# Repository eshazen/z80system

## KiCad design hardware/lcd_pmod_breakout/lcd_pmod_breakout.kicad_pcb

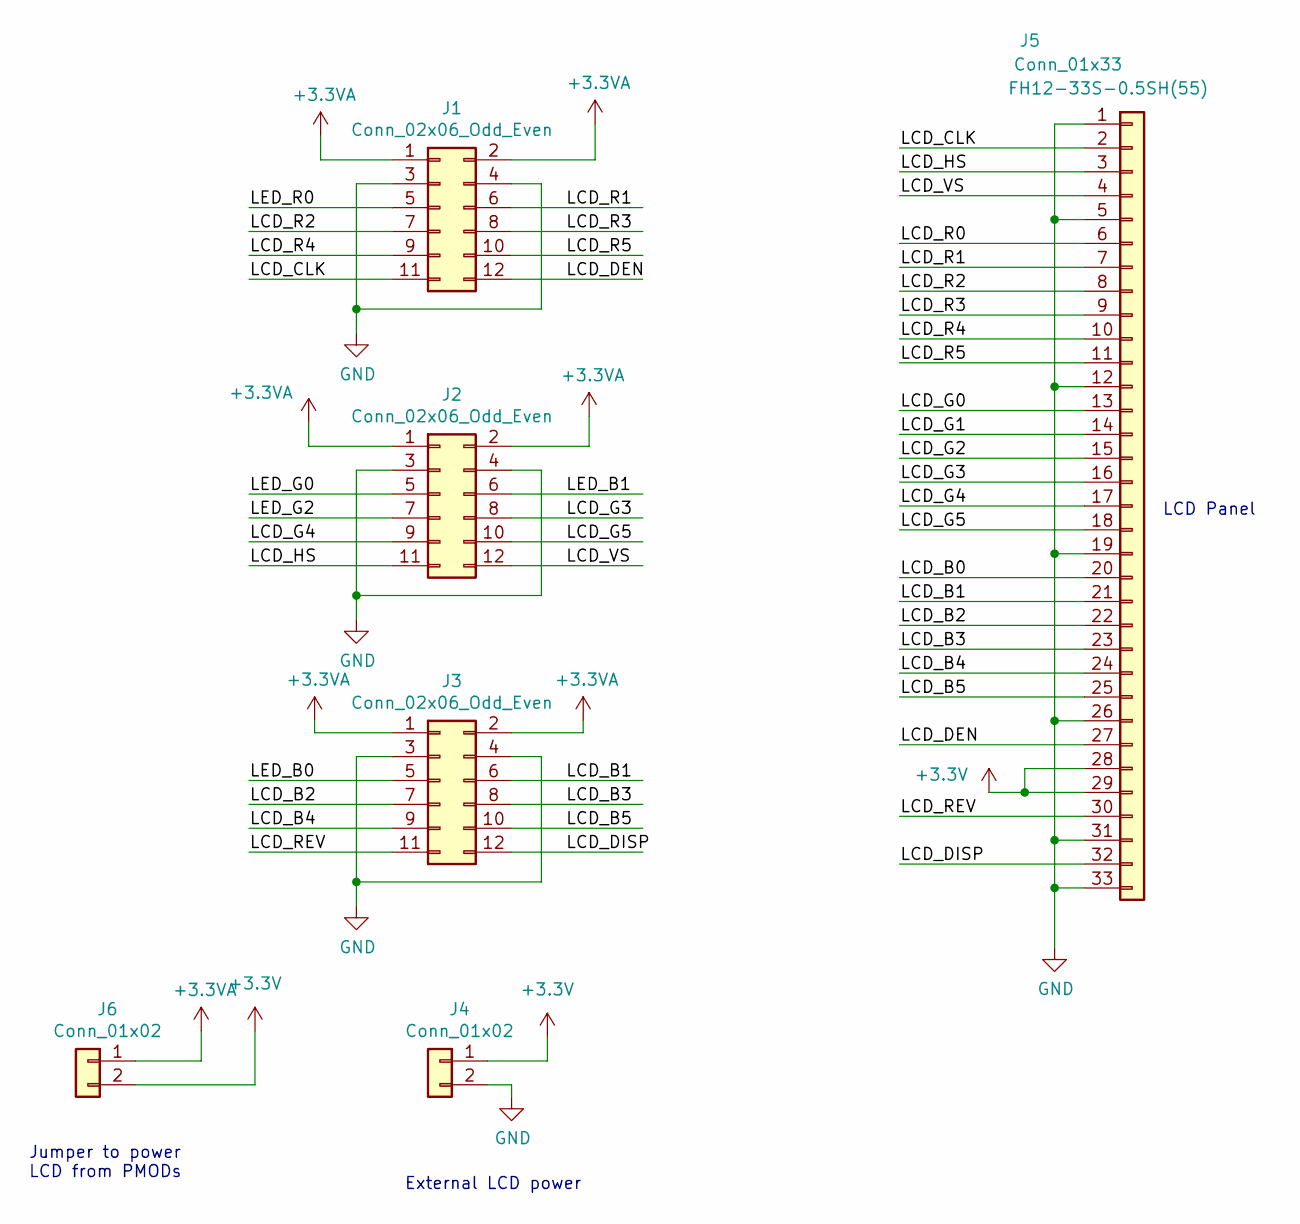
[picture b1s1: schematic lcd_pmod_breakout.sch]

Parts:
J1, J2, J3: Conn_02x06_Odd_Even; PinHeader_2x06_P2.54mm_Vertical
J4, J6: Conn_01x02; PinHeader_1x02_P2.54mm_Vertical
J5: Conn_01x33; FH12-33S-0.5

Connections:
+3.3VA: J1.1, J1.2, J2.1, J2.2, J3.1, J3.2, J6.1
+3V3: J4.1, J5.28, J5.29, J6.2
/LCD_B0: J5.20
/LCD_B1: J3.6, J5.21
/LCD_B2: J3.7, J5.22
/LCD_B3: J3.8, J5.23
/LCD_B4: J3.9, J5.24
/LCD_B5: J3.10, J5.25
/LCD_CLK: J1.11, J5.2
/LCD_DEN: J1.12, J5.27
/LCD_DISP: J3.12, J5.32
/LCD_G0: J5.13
/LCD_G1: J5.14
/LCD_G2: J5.15
/LCD_G3: J2.8, J5.16
/LCD_G4: J2.9, J5.17
/LCD_G5: J2.10, J5.18
/LCD_HS: J2.11, J5.3
/LCD_R0: J5.6
/LCD_R1: J1.6, J5.7
/LCD_R2: J1.7, J5.8
/LCD_R3: J1.8, J5.9
/LCD_R4: J1.9, J5.10
/LCD_R5: J1.10, J5.11
/LCD_REV: J3.11, J5.30
/LCD_VS: J2.12, J5.4
/LED_B0: J3.5
/LED_B1: J2.6
/LED_G0: J2.5
/LED_G2: J2.7
/LED_R0: J1.5
GND: J1.3, J1.4, J2.3, J2.4, J3.3, J3.4, J4.2, J5.1, J5.5, J5.12, J5.19, J5.26, J5.31, J5.33

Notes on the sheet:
LCD Panel
Jumper to power LCD from PMODs
External LCD power

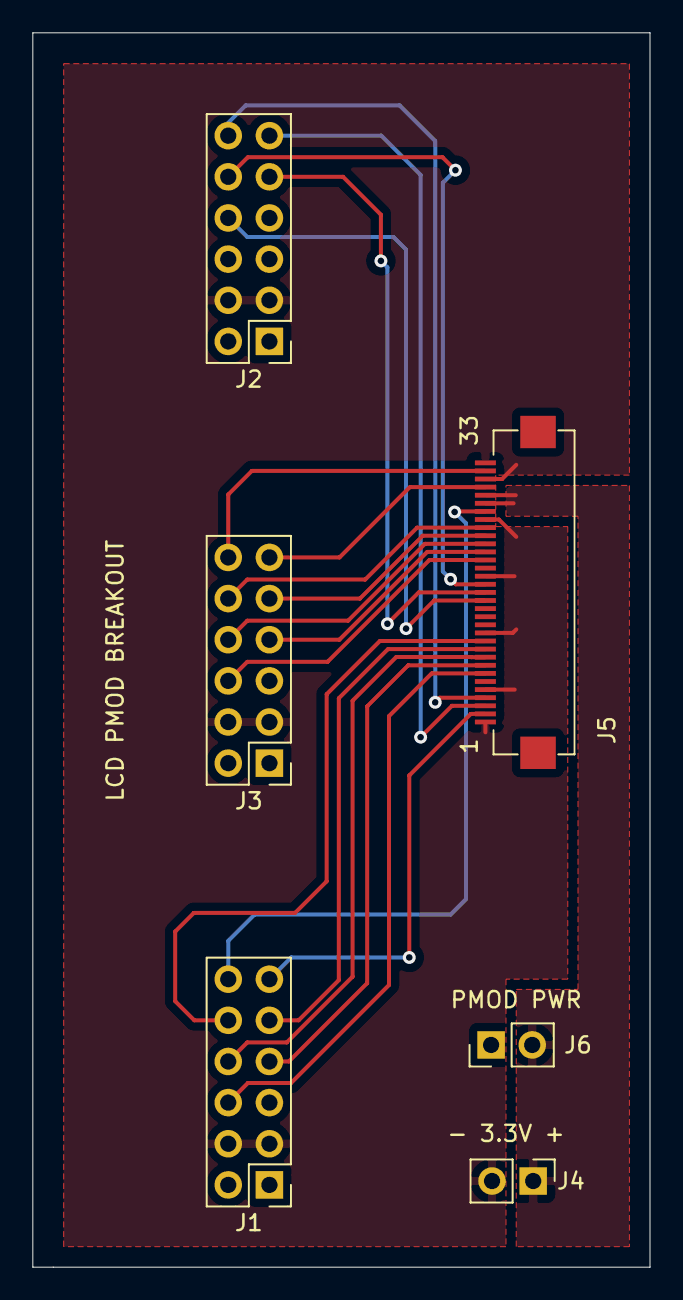
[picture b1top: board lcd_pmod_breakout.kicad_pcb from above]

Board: 2 copper layers, 38.1 x 76.2 mm, 6 parts (0 on the bottom side), 22 nets.

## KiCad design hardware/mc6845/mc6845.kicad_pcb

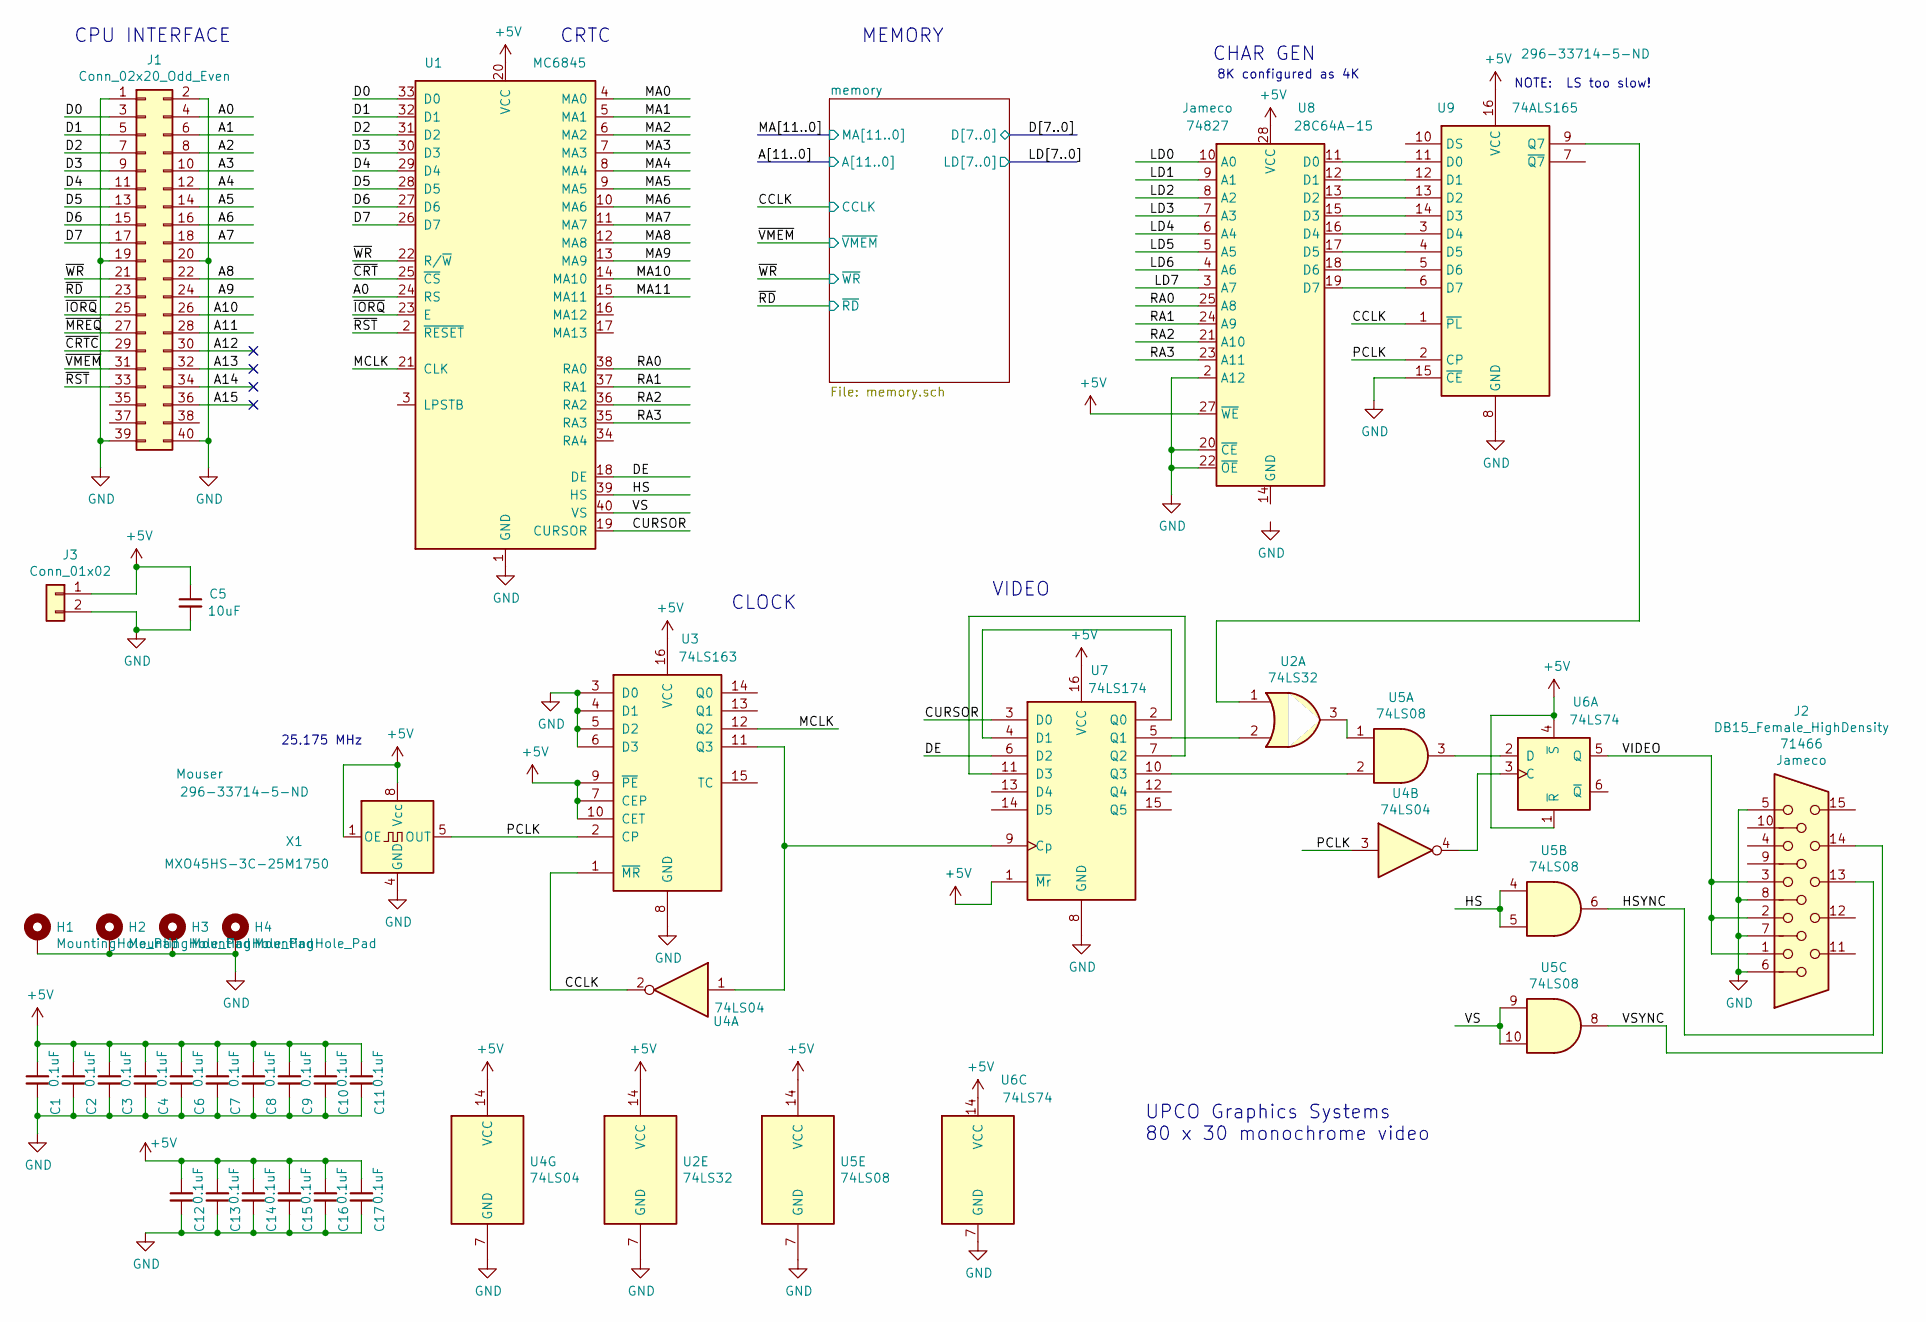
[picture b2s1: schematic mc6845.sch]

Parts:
C1, C2, C3, C4, C6, C7, C8, C9, C10, C11, C12, C13, C14, C15, C16, C17: 0.1uF; C_Disc_D3.0mm_W1.6mm_P2.50mm
C5: 10uF; CP_Radial_Tantal_D5.5mm_P5.00mm
H1, H2, H3, H4: MountingHole_Pad; MountingHole_2.7mm_M2.5_DIN965_Pad
J1: Conn_02x20_Odd_Even; PinSocket_2x20_P2.54mm_Vertical
J2: DB15_Female_HighDensity; DSUB-15-HD_Female_Horizontal_P2.29x2.54mm_EdgePinOffset9.40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
J3: Conn_01x02; Molex_Mini-Fit_Jr_5566-02A_2x01_P4.20mm_Vertical
U1: MC6845; DIP-40_W15.24mm
U2: 74LS32; DIP-14_W7.62mm_Socket_LongPads
U3: 74LS163; DIP-16_W7.62mm_Socket_LongPads
U4: 74LS04; DIP-14_W7.62mm_Socket_LongPads
U5: 74LS08; DIP-14_W7.62mm_Socket_LongPads
U6: 74LS74; DIP-14_W7.62mm_Socket_LongPads
U7: 74LS174; DIP-16_W7.62mm_Socket_LongPads
U8: 28C64A-15; DIP-28_W15.24mm
U9: 74ALS165; DIP-16_W7.62mm_Socket_LongPads
X1: MXO45HS-3C-25M1750; DIP-8_W7.62mm_LongPads

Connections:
+5V: C1.1, C2.1, C3.1, C4.1, C5.1, C6.1, C7.1, C8.1, C9.1, C10.1, C11.1, C12.1, C13.1, C14.1, C15.1, C16.1, C17.1, J3.1, U1.20 (VCC), U2.14 (VCC), U3.7 (CEP), U3.9 (~PE), U3.10 (CET), U3.16 (VCC), U4.14 (VCC), U5.14 (VCC), U6.1 (~R), U6.4 (~S), U6.14 (VCC), U7.1 (~Mr), U7.16 (VCC), U8.27 (~WE), U8.28 (VCC), U9.16 (VCC), X1.1 (OE), X1.8 (Vcc); also elsewhere on the board
/A0: J1.4, U1.24 (RS); also elsewhere on the board
/A1: J1.6; also elsewhere on the board
/A2: J1.8; also elsewhere on the board
/A3: J1.10; also elsewhere on the board
/A4: J1.12; also elsewhere on the board
/A5: J1.14; also elsewhere on the board
/A6: J1.16; also elsewhere on the board
/A7: J1.18; also elsewhere on the board
/A8: J1.22; also elsewhere on the board
/A9: J1.24; also elsewhere on the board
/A10: J1.26; also elsewhere on the board
/A11: J1.28; also elsewhere on the board
/A12: J1.30
/A13: J1.32
/A14: J1.34
/A15: J1.36
/CCLK: U3.1 (~MR), U4.2, U9.1 (~PL); also elsewhere on the board
/CURSOR: U1.19 (CURSOR), U7.3 (D0)
/D0: J1.3, U1.33 (D0); also elsewhere on the board
/D1: J1.5, U1.32 (D1); also elsewhere on the board
/D2: J1.7, U1.31 (D2); also elsewhere on the board
/D3: J1.9, U1.30 (D3); also elsewhere on the board
/D4: J1.11, U1.29 (D4); also elsewhere on the board
/D5: J1.13, U1.28 (D5); also elsewhere on the board
/D6: J1.15, U1.27 (D6); also elsewhere on the board
/D7: J1.17, U1.26 (D7); also elsewhere on the board
/DE: U1.18 (DE), U7.6 (D2)
/HS: U1.39 (HS), U5.4, U5.5
/HSYNC: J2.13, U5.6
/LD0: U8.10 (A0); also elsewhere on the board
/LD1: U8.9 (A1); also elsewhere on the board
/LD2: U8.8 (A2); also elsewhere on the board
/LD3: U8.7 (A3); also elsewhere on the board
/LD4: U8.6 (A4); also elsewhere on the board
/LD5: U8.5 (A5); also elsewhere on the board
/LD6: U8.4 (A6); also elsewhere on the board
/LD7: U8.3 (A7); also elsewhere on the board
/MA0: U1.4 (MA0); also elsewhere on the board
/MA1: U1.5 (MA1); also elsewhere on the board
/MA2: U1.6 (MA2); also elsewhere on the board
/MA3: U1.7 (MA3); also elsewhere on the board
/MA4: U1.8 (MA4); also elsewhere on the board
/MA5: U1.9 (MA5); also elsewhere on the board
/MA6: U1.10 (MA6); also elsewhere on the board
/MA7: U1.11 (MA7); also elsewhere on the board
/MA8: U1.12 (MA8); also elsewhere on the board
/MA9: U1.13 (MA9); also elsewhere on the board
/MA10: U1.14 (MA10); also elsewhere on the board
/MA11: U1.15 (MA11); also elsewhere on the board
/MCLK: U1.21 (CLK), U3.12 (Q2)
/PCLK: U3.2 (CP), U4.3, U9.2 (CP), X1.5 (OUT)
/RA0: U1.38 (RA0), U8.25 (A8)
/RA1: U1.37 (RA1), U8.24 (A9)
/RA2: U1.36 (RA2), U8.21 (A10)
/RA3: U1.35 (RA3), U8.23 (A11)
/VIDEO: J2.1, J2.2, J2.3, U6.5 (Q)
/VS: U1.40 (VS), U5.9, U5.10
/VSYNC: J2.14, U5.8
/~CRT: U1.25 (~CS)
/~CRTC: J1.29
/~IORQ: J1.25, U1.23 (E)
/~MREQ: J1.27
/~RD: J1.23; also elsewhere on the board
/~RST: J1.33, U1.2 (~RESET)
/~VMEM: J1.31; also elsewhere on the board
/~WR: J1.21, U1.22 (R/~W); also elsewhere on the board
GND: C1.2, C2.2, C3.2, C4.2, C5.2, C6.2, C7.2, C8.2, C9.2, C10.2, C11.2, C12.2, C13.2, C14.2, C15.2, C16.2, C17.2, H1.1, H2.1, H3.1, H4.1, J1.1, J1.2, J1.19, J1.20, J1.39, J1.40, J2.5, J2.6, J2.7, J2.8, J3.2, U1.1 (GND), U2.7 (GND), U3.3 (D0), U3.4 (D1), U3.5 (D2), U3.6 (D3), U3.8 (GND), U4.7 (GND), U5.7 (GND), U6.7 (GND), U7.8 (GND), U8.2 (A12), U8.20 (~CE), U8.22 (~OE), U9.8 (GND), U9.15 (~CE), X1.4 (GND); also elsewhere on the board
unnamed: U2.1, U9.9 (Q7)
unnamed: U2.2, U7.5 (Q1)
unnamed: U2.3, U5.1
unnamed: U3.11 (Q3), U4.1, U7.9 (Cp)
unnamed: U4.4, U6.3 (C)
unnamed: U5.2, U7.10 (Q3)
unnamed: U5.3, U6.2 (D)
unnamed: U7.2 (Q0), U7.4 (D1)
unnamed: U7.7 (Q2), U7.11 (D3)
unnamed: U8.11 (D0), U9.11 (D0)
unnamed: U8.12 (D1), U9.12 (D1)
unnamed: U8.13 (D2), U9.13 (D2)
unnamed: U8.15 (D3), U9.14 (D3)
unnamed: U8.16 (D4), U9.3 (D4)
unnamed: U8.17 (D5), U9.4 (D5)
unnamed: U8.18 (D6), U9.5 (D6)
unnamed: U8.19 (D7), U9.6 (D7)

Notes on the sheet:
CPU INTERFACE
NOTE: LS too slow!
CLOCK
VIDEO
CRTC
MEMORY
CHAR GEN
25.175 MHz
8K configured as 4K
UPCO Graphics Systems 80 x 30 monochrome video

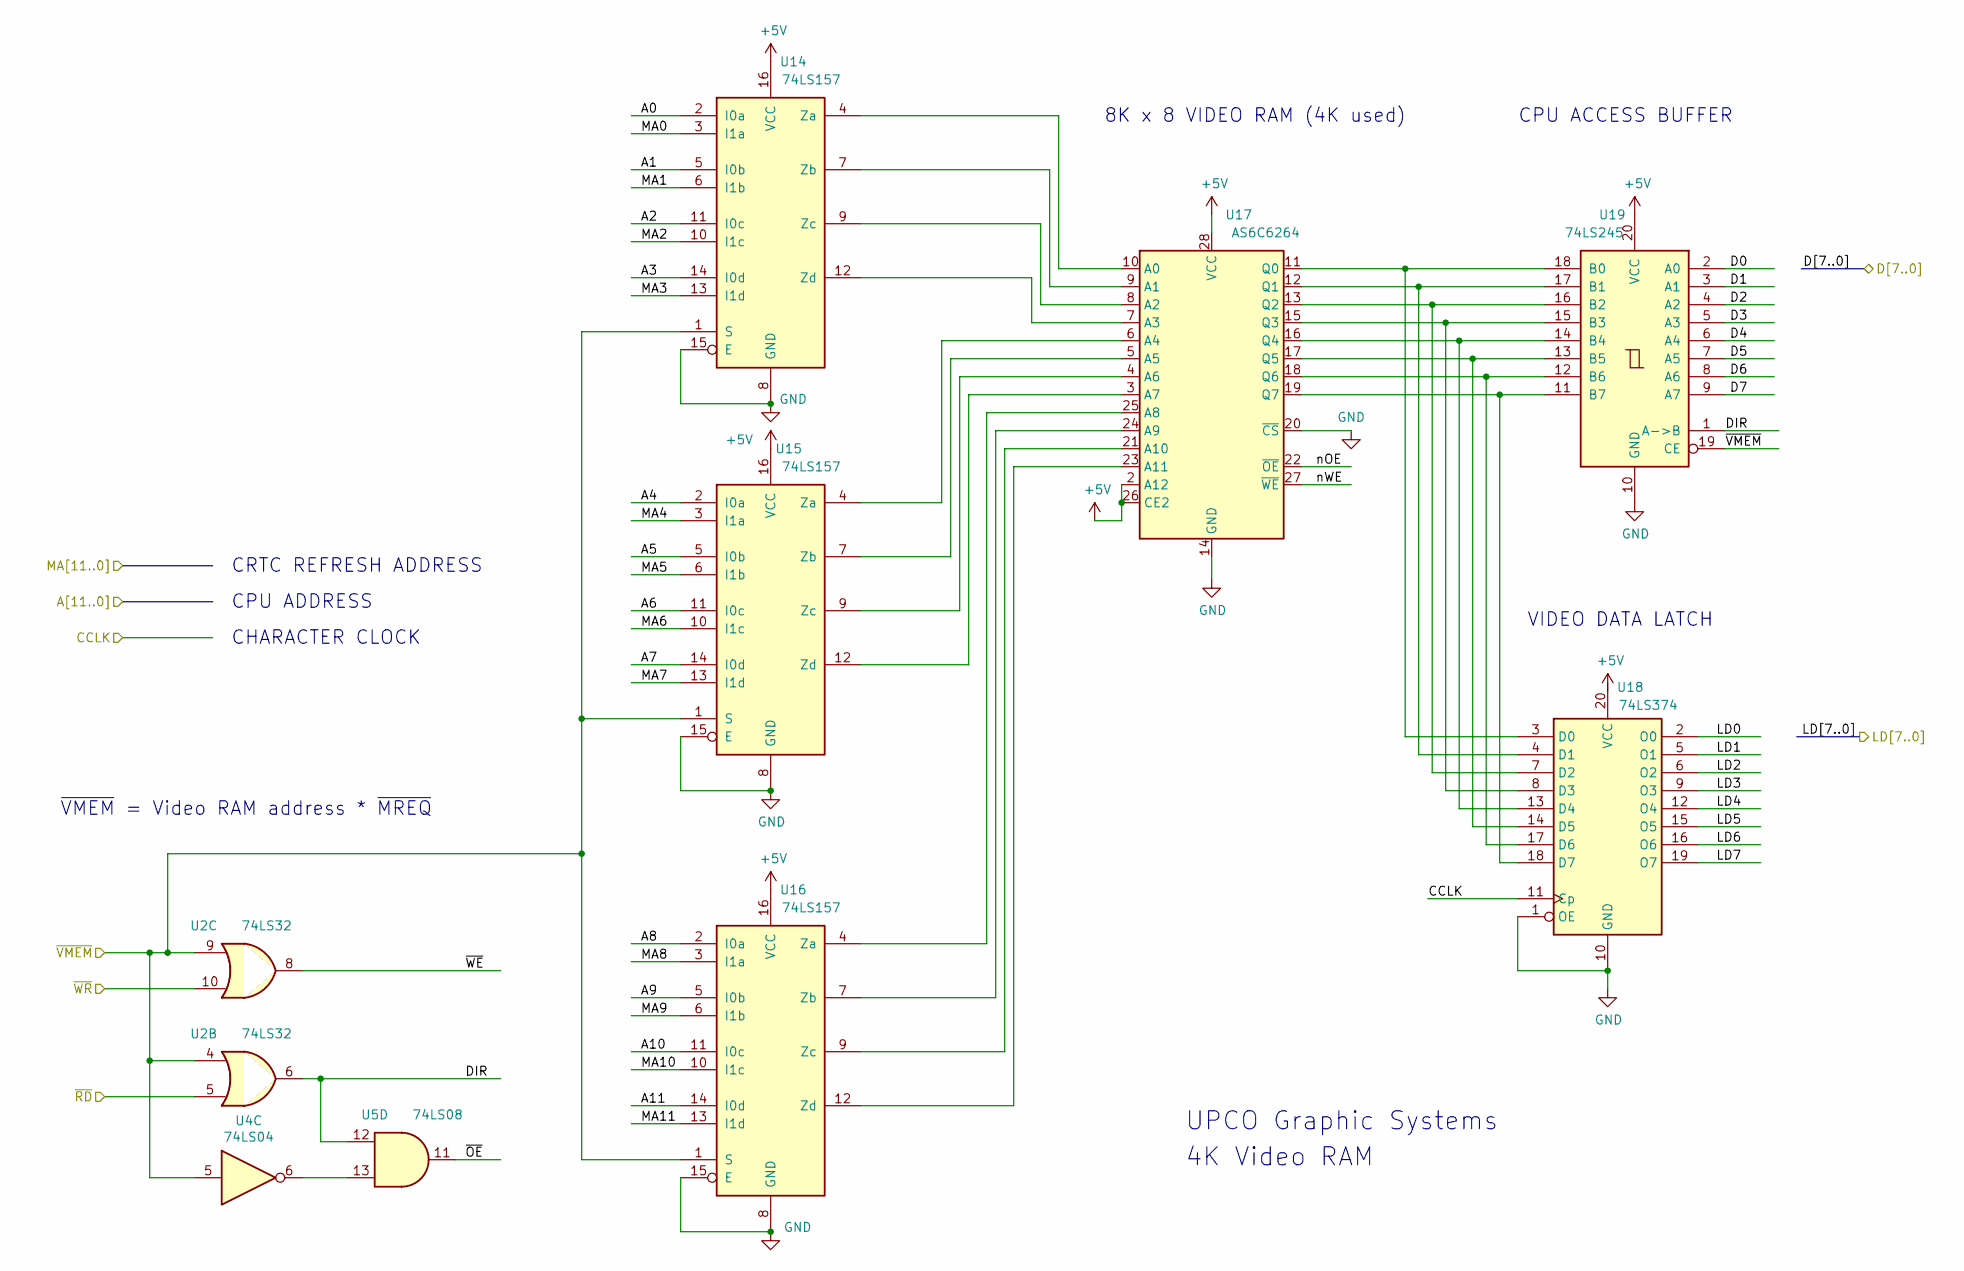
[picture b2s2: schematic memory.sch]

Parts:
U2: 74LS32; DIP-14_W7.62mm_Socket_LongPads
U4: 74LS04; DIP-14_W7.62mm_Socket_LongPads
U5: 74LS08; DIP-14_W7.62mm_Socket_LongPads
U14, U15, U16: 74LS157; DIP-16_W7.62mm_Socket_LongPads
U17: AS6C6264; DIP-28_W15.24mm
U18: 74LS374; DIP-20_W7.62mm_Socket_LongPads
U19: 74LS245; DIP-20_W7.62mm_Socket_LongPads

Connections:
+5V: U14.16 (VCC), U15.16 (VCC), U16.16 (VCC), U17.2 (A12), U17.26 (CE2), U17.28 (VCC), U19.20 (VCC); also elsewhere on the board
/A0: U14.2 (I0a); also elsewhere on the board
/A1: U14.5 (I0b); also elsewhere on the board
/A2: U14.11 (I0c); also elsewhere on the board
/A3: U14.14 (I0d); also elsewhere on the board
/A4: U15.2 (I0a); also elsewhere on the board
/A5: U15.5 (I0b); also elsewhere on the board
/A6: U15.11 (I0c); also elsewhere on the board
/A7: U15.14 (I0d); also elsewhere on the board
/A8: U16.2 (I0a); also elsewhere on the board
/A9: U16.5 (I0b); also elsewhere on the board
/A10: U16.11 (I0c); also elsewhere on the board
/A11: U16.14 (I0d); also elsewhere on the board
/CCLK: U18.11 (Cp); also elsewhere on the board
/D0: U19.2 (A0); also elsewhere on the board
/D1: U19.3 (A1); also elsewhere on the board
/D2: U19.4 (A2); also elsewhere on the board
/D3: U19.5 (A3); also elsewhere on the board
/D4: U19.6 (A4); also elsewhere on the board
/D5: U19.7 (A5); also elsewhere on the board
/D6: U19.8 (A6); also elsewhere on the board
/D7: U19.9 (A7); also elsewhere on the board
/LD0: U18.2 (O0); also elsewhere on the board
/LD1: U18.5 (O1); also elsewhere on the board
/LD2: U18.6 (O2); also elsewhere on the board
/LD3: U18.9 (O3); also elsewhere on the board
/LD4: U18.12 (O4); also elsewhere on the board
/LD5: U18.15 (O5); also elsewhere on the board
/LD6: U18.16 (O6); also elsewhere on the board
/LD7: U18.19 (O7); also elsewhere on the board
/MA0: U14.3 (I1a); also elsewhere on the board
/MA1: U14.6 (I1b); also elsewhere on the board
/MA2: U14.10 (I1c); also elsewhere on the board
/MA3: U14.13 (I1d); also elsewhere on the board
/MA4: U15.3 (I1a); also elsewhere on the board
/MA5: U15.6 (I1b); also elsewhere on the board
/MA6: U15.10 (I1c); also elsewhere on the board
/MA7: U15.13 (I1d); also elsewhere on the board
/MA8: U16.3 (I1a); also elsewhere on the board
/MA9: U16.6 (I1b); also elsewhere on the board
/MA10: U16.10 (I1c); also elsewhere on the board
/MA11: U16.13 (I1d); also elsewhere on the board
/memory/DIR: U2.6, U5.12, U19.1 (A->B)
/memory/nOE: U17.22 (~OE)
/memory/nWE: U17.27 (~WE)
/memory/~OE: U5.11
/memory/~WE: U2.8
/~RD: U2.5; also elsewhere on the board
/~VMEM: U2.4, U2.9, U4.5, U14.1 (S), U15.1 (S), U16.1 (S), U19.19 (CE); also elsewhere on the board
/~WR: U2.10; also elsewhere on the board
GND: U14.8 (GND), U14.15 (E), U15.8 (GND), U15.15 (E), U16.8 (GND), U16.15 (E), U17.14 (GND), U17.20 (~CS), U18.1 (OE), U18.10 (GND), U19.10 (GND); also elsewhere on the board
unnamed: U4.6, U5.13
unnamed: U14.4 (Za), U17.10 (A0)
unnamed: U14.7 (Zb), U17.9 (A1)
unnamed: U14.9 (Zc), U17.8 (A2)
unnamed: U14.12 (Zd), U17.7 (A3)
unnamed: U15.4 (Za), U17.6 (A4)
unnamed: U15.7 (Zb), U17.5 (A5)
unnamed: U15.9 (Zc), U17.4 (A6)
unnamed: U15.12 (Zd), U17.3 (A7)
unnamed: U16.4 (Za), U17.25 (A8)
unnamed: U16.7 (Zb), U17.24 (A9)
unnamed: U16.9 (Zc), U17.21 (A10)
unnamed: U16.12 (Zd), U17.23 (A11)
unnamed: U17.11 (Q0), U18.3 (D0), U19.18 (B0)
unnamed: U17.12 (Q1), U18.4 (D1), U19.17 (B1)
unnamed: U17.13 (Q2), U18.7 (D2), U19.16 (B2)
unnamed: U17.15 (Q3), U18.8 (D3), U19.15 (B3)
unnamed: U17.16 (Q4), U18.13 (D4), U19.14 (B4)
unnamed: U17.17 (Q5), U18.14 (D5), U19.13 (B5)
unnamed: U17.18 (Q6), U18.17 (D6), U19.12 (B6)
unnamed: U17.19 (Q7), U18.18 (D7), U19.11 (B7)

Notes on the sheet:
UPCO Graphic Systems
4K Video RAM
8K x 8 VIDEO RAM (4K used)
CPU ACCESS BUFFER
VIDEO DATA LATCH
CRTC REFRESH ADDRESS
CPU ADDRESS
CHARACTER CLOCK
~VMEM~ = Video RAM address * ~MREQ

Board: 2 copper layers, 40 parts (0 on the bottom side), 100 nets, no tracks yet.
